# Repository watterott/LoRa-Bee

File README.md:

# LoRa-Bee
XBee footprint compatible LoRa Module with HopeRF RFM9xW LoRa (Long Range) Wireless Transceiver.

* [HopeRF RFM95W/RFM96W](https://www.hoperf.com/modules/lora/index.html) LoRa Transceiver
* SPI interface
* XBee compatible Pinout (3.3V)
* Open-Source and released under the [Creative Commons Attribution Share-Alike License](https://creativecommons.org/licenses/by-sa/4.0/).
* **[Documentation on learn.watterott.com](https://learn.watterott.com)**

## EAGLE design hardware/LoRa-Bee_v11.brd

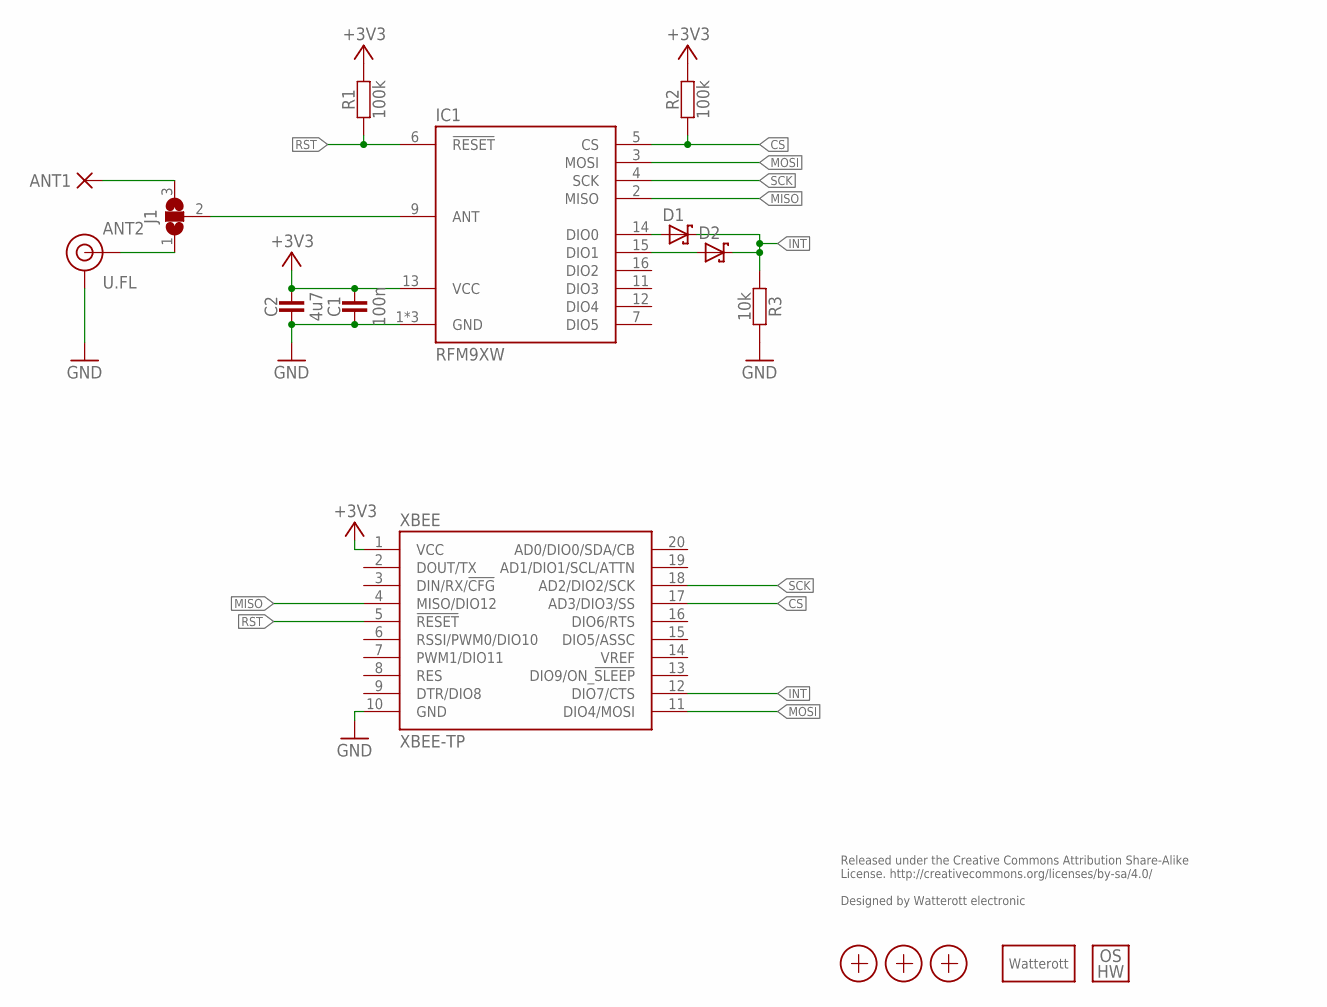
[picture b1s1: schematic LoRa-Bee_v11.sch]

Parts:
ANT1: PAD-1.00-1.60
ANT2: U.FL
C1: 100n; C0402
C2: 4u7; C0402
D1, D2: D_SCHOTTKY-SOD532; SOD523
IC1: RFM9XW; RFM9X
J1: JUMPER3-0603
LOGO3: LOGO_SPARK-2; SPARK_2MM
LOGO4: LOGO_OSHW-2; OSHW_2MM
R1, R2: 100k; C0402
R3: 10k; C0402
X1, X2, X3: PASSER-07; PASSER_07MM
XBEE: XBEE-TP; XBEE_TP

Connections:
+3V3: C1.2, C2.2, IC1.13 (VCC), R1.2, R2.2, XBEE.1 (VCC)
ANT: IC1.9 (ANT), J1.2
CS: IC1.5 (CS), R2.1, XBEE.17 (AD3/DIO3/SS)
GND: ANT2.1 (GND), ANT2.2 (GND), C1.1, C2.1, IC1.1 (GND), IC1.8 (GND), IC1.10 (GND), R3.2, XBEE.10 (GND)
INT: D1.C, D2.C, R3.1, XBEE.12 (DIO7/CTS)
MISO: IC1.2 (MISO), XBEE.4 (MISO/DIO12)
MOSI: IC1.3 (MOSI), XBEE.11 (DIO4/MOSI)
unnamed: D1.A, IC1.14 (DIO0)
unnamed: D2.A, IC1.15 (DIO1)
unnamed: ANT2.FEED (SIGNAL), J1.1
unnamed: ANT1.1, J1.3
RST: IC1.6 (!RESET), R1.1, XBEE.5 (!RESET!)
SCK: IC1.4 (SCK), XBEE.18 (AD2/DIO2/SCK)

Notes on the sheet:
Released under the Creative Commons Attribution Share-Alike License. http://creativecommons.org/licenses/by-sa/4.0/ Designed by Watterott electronic

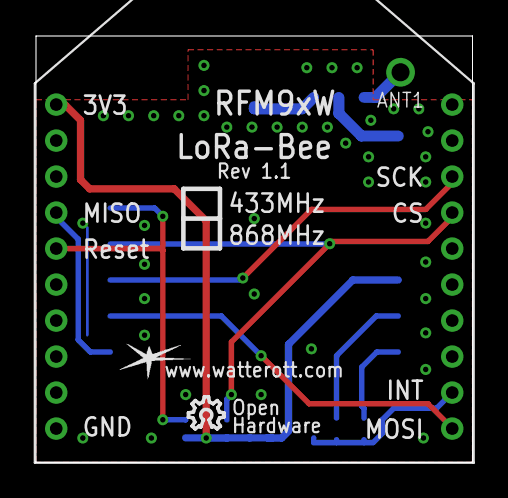
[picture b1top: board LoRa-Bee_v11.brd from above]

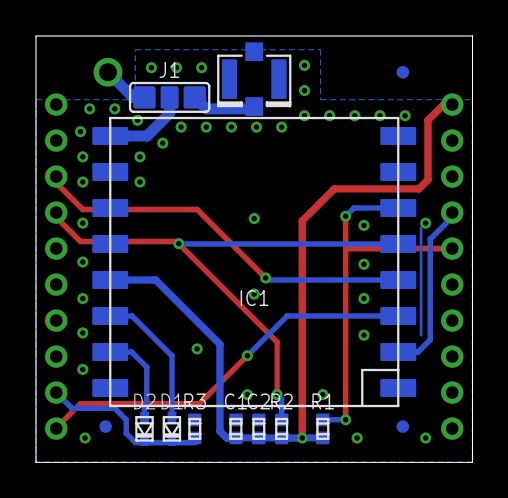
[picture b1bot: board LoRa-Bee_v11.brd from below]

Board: 2 copper layers, 24.2 x 23.7 mm, 17 parts (13 on the bottom side), 13 nets.

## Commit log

2017-09-12 added readme
2018-05-03 added layout and schematics
2018-10-27 updated schematics
2019-05-14 added picture
